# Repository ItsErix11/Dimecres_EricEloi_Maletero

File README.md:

View this project on [CADLAB.io](https://cadlab.io/project/29036). 

# Proyecto Maletero

## Autores
- Eric Trejo Sanchez (@ItsErix11)
- Eloi Ortega Ortiz (@EloiOrtega)

## Versió - v1.0 ## Curs - Assignatura de Disseny de PCBs amb KiCad - [Curs 2024-2025]

## Objetivo 
Nuestro objetivo es crear un sistema controlador del maletero de un coche que pueda cumplir las funciones de abrir y cerrar el maletero con un motor, desempañar el cristal de este y que se pueda abrir con un sensor con el pie en el caso de tener las manos ocupadas

## Requisitos i especificaciones
- Control del motor de apertura/cierre del maletero
- Sistema de calefacción para desempañar el cristal
- Sensor de movimiento para apertura sin contacto
- Interfaz CAN para comunicación con otros sistemas del coche
- Protección contra sobrecorriente en el control del motor

## Diagrama de bloques 

## Tabla de componentes
| Descripció | Manufacturer Number | Package | Datasheet | Proveïdor | Unitats |
|------------|--------------------|---------|----------|----------|---------|
| LDO Voltage Regulators 5A L Drop Pos Fixed Regs | LT1084CT-5 | TO-220 | https://eu.mouser.com/datasheet/2/609/1083ffe-3123432.pdf | DigiKey | 1 |
| MCU 32 KB FL 1536 RAM 25 I/O | PIC18F2580T-I/SO | SOIC-28 | https://eu.mouser.com/datasheet/2/268/39637d-3443674.pdf | DigiKey | 1 |
| Impulsor de motor Unipolar NMOS PWM 8-SO-PowerPad | DRV8870DDA | HTSSOP-8 | https://www.ti.com/lit/ds/symlink/drv8870.pdf?HQS=dis-dk-null-digikeymode-dsf-pf-null-wwe&ts=1745209885777 | DigiKey | 1 |
| CAN Interface IC Hi Spd CAN Transceiv | MCP2551-I/SN | SOIC-8 | https://eu.mouser.com/datasheet/2/268/20001667G-3441642.pdf | DigiKey | 1 |
| Operational Amplifiers - Op Amps LOW PWR SGL OP AMP A 926-LM321MF/NOPB | LM321MFX/NOPB | SOT-23-5 | https://www.ti.com/lit/ds/symlink/lm321.pdf?ts=1742974140204&ref_url=https%253A%252F%252Fwww.ti.com%252Fproduct%252FLM321%253FkeyMatch%253DLM321%2526tisearch%253Duniversal_search%2526usecase%253DGPN-ALT | DigiKey | 1 |

## Funcionalidades
1. **Control del maletero**:
   - Apertura y cierre mediante motor controlado por el MCU
   - Protección antipinch mediante detección de corriente
   
2. **Sistema de desempañado**:
   - Calefacción controlada por botones para regulación de temperatura
   
3. **Apertura sin contacto**:
   - Sensor de movimiento para detección del pie

4. **Interfaz de comunicación**:
   - Protocolo CAN para integración con otros sistemas del coche
   - Posibilidad de control remoto desde la llave o panel central

## Historial de cambios 
| Data | Autor | Branch | Descripció |
|------|------|--------|------------|
| 2025-04-24 | Eric | `main` | Orden final, final del readme |
| 2025-04-24 | Eloi | `main` | Ultima revisión |
| 2025-04-23 | Eric | `main` | Version final final |
| 2025-04-23 | Eric | `main` | Todos los arreglos del placement |
| 2025-04-22 | Eric | `main` | Textos de fabrica y reglas de diseño solucionado |
| 2025-04-22 | Eric | `main` | Orden de carpetas y referencia a autores (nosotros) |
| 2025-04-21 | Eric | `main` | Inicio presupuesto y continuación del readme |
| 2025-04-18 | Eloi | `main` | Actualización del layout |
| 2025-04-17 | Eloi | `main` | Actualización del layout y netclases |
| 2025-04-12 | Eric | `main` | Orden carpetas |
| 2025-04-12 | Eric | `main` | Diagrama completo |
| 2025-04-09 | Eric | `main` | Esquematico final y pasado al layout |
| 2025-04-09 | Eric | `main` | Orden del esquematico |
| 2025-04-09 | Eric | `main` | Esquematico compactado |
| 2025-04-09 | Eloi | `main` | Corrección de errores de clase |
| 2025-04-09 | Eric | `main` | DRC errores 0, warnings 25 |
| 2025-04-09 | Eloi | `main` | Ultimos ajustes de islas del GND |
| 2025-04-08 | Eloi | `main` | Actualización de huella |
| 2025-04-08 | Eric | `main` | Reglas de diseño, 0 errores y separación de componentes |
| 2025-04-08 | Eric | `main` | Par diferencial CAN |
| 2025-04-08 | Eloi | `main` | Corrección de reglas de diseño del layout | 
| 2025-04-04 | Eloi | `main` | Layout v1.2 acabado |
| 2025-04-02 | Eloi | `main` | Corrección de errores del layout |
| 2025-04-02 | Eric | `main` | Esquematico y diagrama acabados |
| 2025-04-01 | Eloi | `main` | Layout final v.1, routing terminado |
| 2025-04-01 | Eric | `main` | Arreglos del GNDPWR y GND |
| 2025-04-01 | Eloi | `main` | Actualización del layout, capas top suprimidas |
| 2025-04-01 | Eric | `main` | Capas de cobre del layout y DE-9 |
| 2025-04-01 | Eloi | `main` | Actualización del layout |
| 2025-04-01 | Eloi | `main` | Layout placement |
| 2025-04-01 | Eloi | `main` | Creación del layout |
| 2025-04-01 | Eric | `main` | Arreglos esquemático |
| 2025-04-01 | Eloi | `main` | Huellas añadidas al esquematico |
| 2025-04-01 | Eloi | `main` | Cambio de sensor en el esquemático |
| 2025-03-31 | Eric | `main` | Adición del DE-9 y regulador del sensor del esquemático|
| 2025-03-30 | Eloi | `main` | Corrección de errores del esquemático |
| 2025-03-30 | Eric | `main` | Esquemático ordenado |
| 2025-03-29 | Eloi | `main` | Corrección del switch y net lists del esquemático |
| 2025-03-29 | Eric | `main` | Mas correcciones del esquemático |
| 2025-03-27 | Eric | `main` | Correcciones de orden y conectores del esquemático|
| 2025-03-26 | Eloi | `main` | Adición de Net lists, corrección de errores y regulador de tensión del esquematico |
| 2025-03-25 | Eric | `main` | Conector del Program |
| 2025-03-25 | Eric | `main` | Diagrama de bloques añadido |
| 2025-03-25 | Eric | `main` | Rth mas disperso |
| 2025-03-25 | Eric | `main` | Corrección del CAN y separación |
| 2025-03-25 | Eric | `main` | Adición de condensadores de desacoplo |
| 2025-03-25 | Eloi | `main` | Versión casi final |
| 2025-03-25 | Eric | `main` | Transcriver CAN, casi todo el MCU completado |
| 2025-03-24 | Eloi | `main` | Corrección de errores |
| 2025-03-24 | Eloi | `main` | Resistencia termica añadida |
| 2025-03-24 | Eric | `main` | Pruebas del proyecto |
| 2025-03-24 | Eric | `main` | Cristal añadido |
| 2025-03-24 | Eric | `main` | Reorganización y corrección de errores |
| 2025-03-24 | Eloi | `main` | Etapa de regulación (LT1117) |
| 2025-03-24 | Eric | `main` | Adición de conectores |
| 2025-03-24 | Eric | `main` | Creación del proyecto |

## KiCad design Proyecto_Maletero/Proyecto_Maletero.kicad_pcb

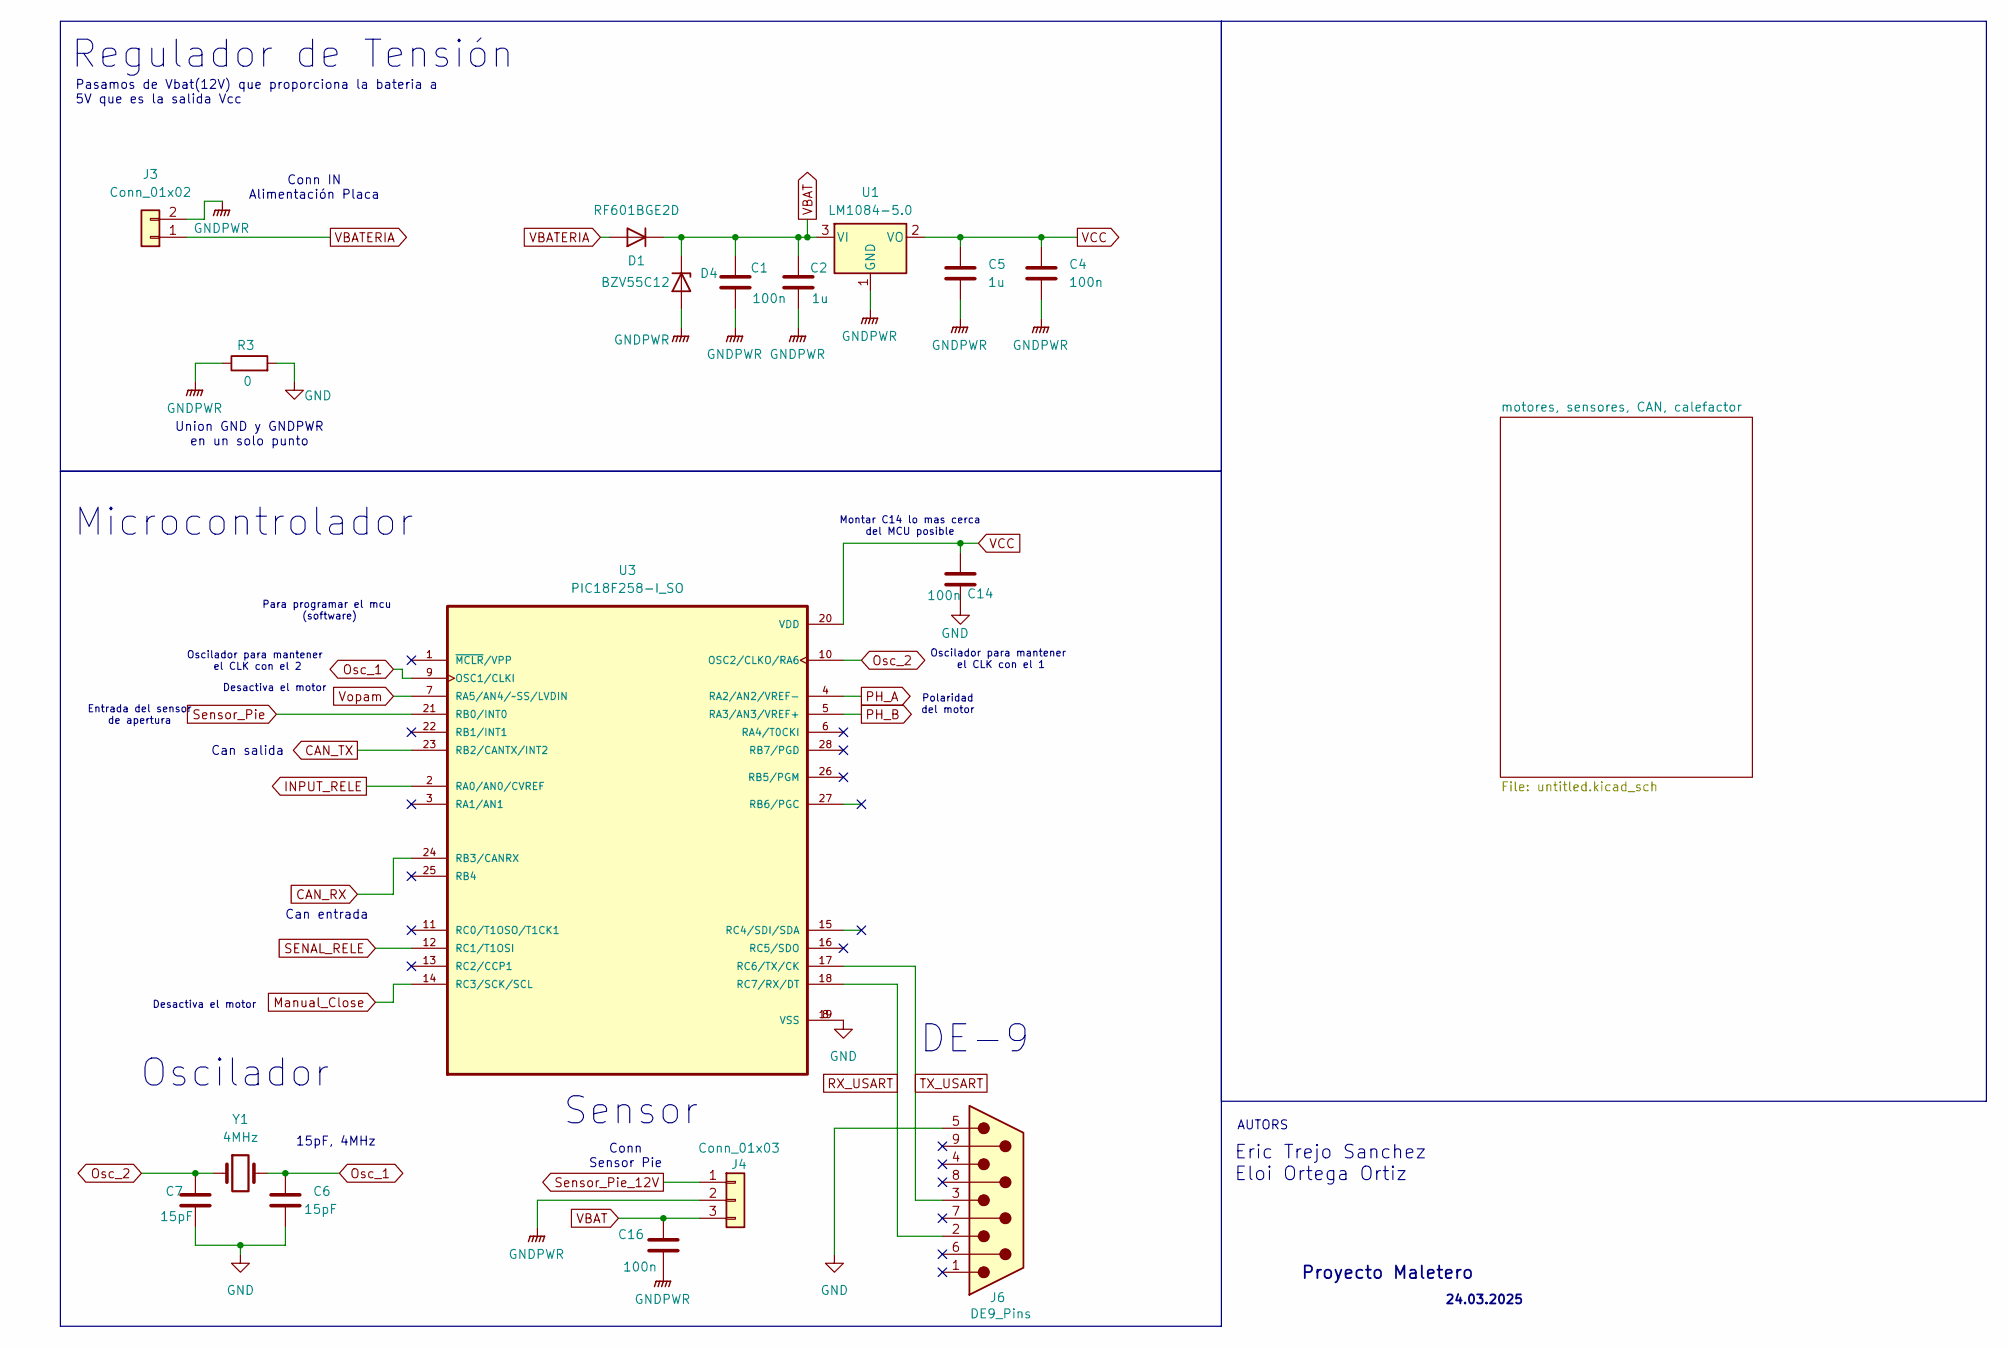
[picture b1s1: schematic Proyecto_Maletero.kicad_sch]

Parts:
C1, C4, C14, C16: 100n; C_0805_2012Metric
C2, C5: 1u; C_0805_2012Metric
C6, C7: 15pF; C_0805_2012Metric
D1: RF601BGE2D; D_0805_2012Metric
D4: BZV55C12; D_MiniMELF
J3: Conn_01x02; TerminalBlock_Phoenix_MKDS-1,5-2-5.08_1x02_P5.08mm_Horizont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
J4: Conn_01x03; TerminalBlock_Phoenix_MKDS-1,5-3_1x03_P5.00mm_Horizontal
J6: DE9_Pins; DSUB-9_Pins_Horizontal_P2.77x2.54mm_EdgePinOffset9.40mm
R3: 0
U1: LM1084-5.0; LT1117
U3: PIC18F258-I_SO; SOIC127P1030X265-28N
Y1: 4MHz; Crystal_SMD_HC49-SD

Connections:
CAN_RX: U3.24 (RB3/CANRX); also elsewhere on the board
CAN_TX: U3.23 (RB2/CANTX/INT2); also elsewhere on the board
GND: C6.2, C7.2, C14.1, J6.5, R3.2, U3.8 (VSS), U3.19 (VSS); also elsewhere on the board
GNDPWR: C1.2, C2.2, C4.2, C5.2, C16.1, D4.2 (A), J3.2, J4.2, R3.1, U1.1 (GND); also elsewhere on the board
INPUT_RELE: U3.2 (RA0/AN0/CVREF); also elsewhere on the board
Manual_Close: U3.14 (RC3/SCK/SCL); also elsewhere on the board
Osc_1: C6.1, U3.9 (OSC1/CLKI), Y1.2
Osc_2: C7.1, U3.10 (OSC2/CLKO/RA6), Y1.1
PH_A: U3.4 (RA2/AN2/VREF-); also elsewhere on the board
PH_B: U3.5 (RA3/AN3/VREF+); also elsewhere on the board
RX_USART: J6.2, U3.18 (RC7/RX/DT)
SENAL_RELE: U3.12 (RC1/T1OSI); also elsewhere on the board
Sensor_Pie: U3.21 (RB0/INT0); also elsewhere on the board
Sensor_Pie_12V: J4.1; also elsewhere on the board
TX_USART: J6.3, U3.17 (RC6/TX/CK)
VBAT: C1.1, C2.1, C16.2, D1.1 (K), D4.1 (K), J4.3, U1.3 (VI); also elsewhere on the board
VBATERIA: D1.2 (A), J3.1
VCC: C4.1, C5.1, C14.2, U1.2 (VO), U3.20 (VDD); also elsewhere on the board
Vopam: U3.7 (RA5/AN4/~SS/LVDIN); also elsewhere on the board

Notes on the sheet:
Desactiva el motor
Para programar el mcu (software)
Polaridad del motor
Eric Trejo Sanchez Eloi Ortega Ortiz
DE-9
Regulador de Tensión
Pasamos de Vbat(12V) que proporciona la bateria a 5V que es la salida Vcc
Microcontrolador
Sensor
Union GND y GNDPWR en un solo punto
15pF, 4MHz
Oscilador para mantener el CLK con el 1
Entrada del sensor de apertura
Can salida
Oscilador
Proyecto Maletero
Montar C14 lo mas cerca del MCU posible
Can entrada
AUTORS
24.03.2025
Oscilador para mantener el CLK con el 2
Conn IN Alimentación Placa
Conn Sensor Pie

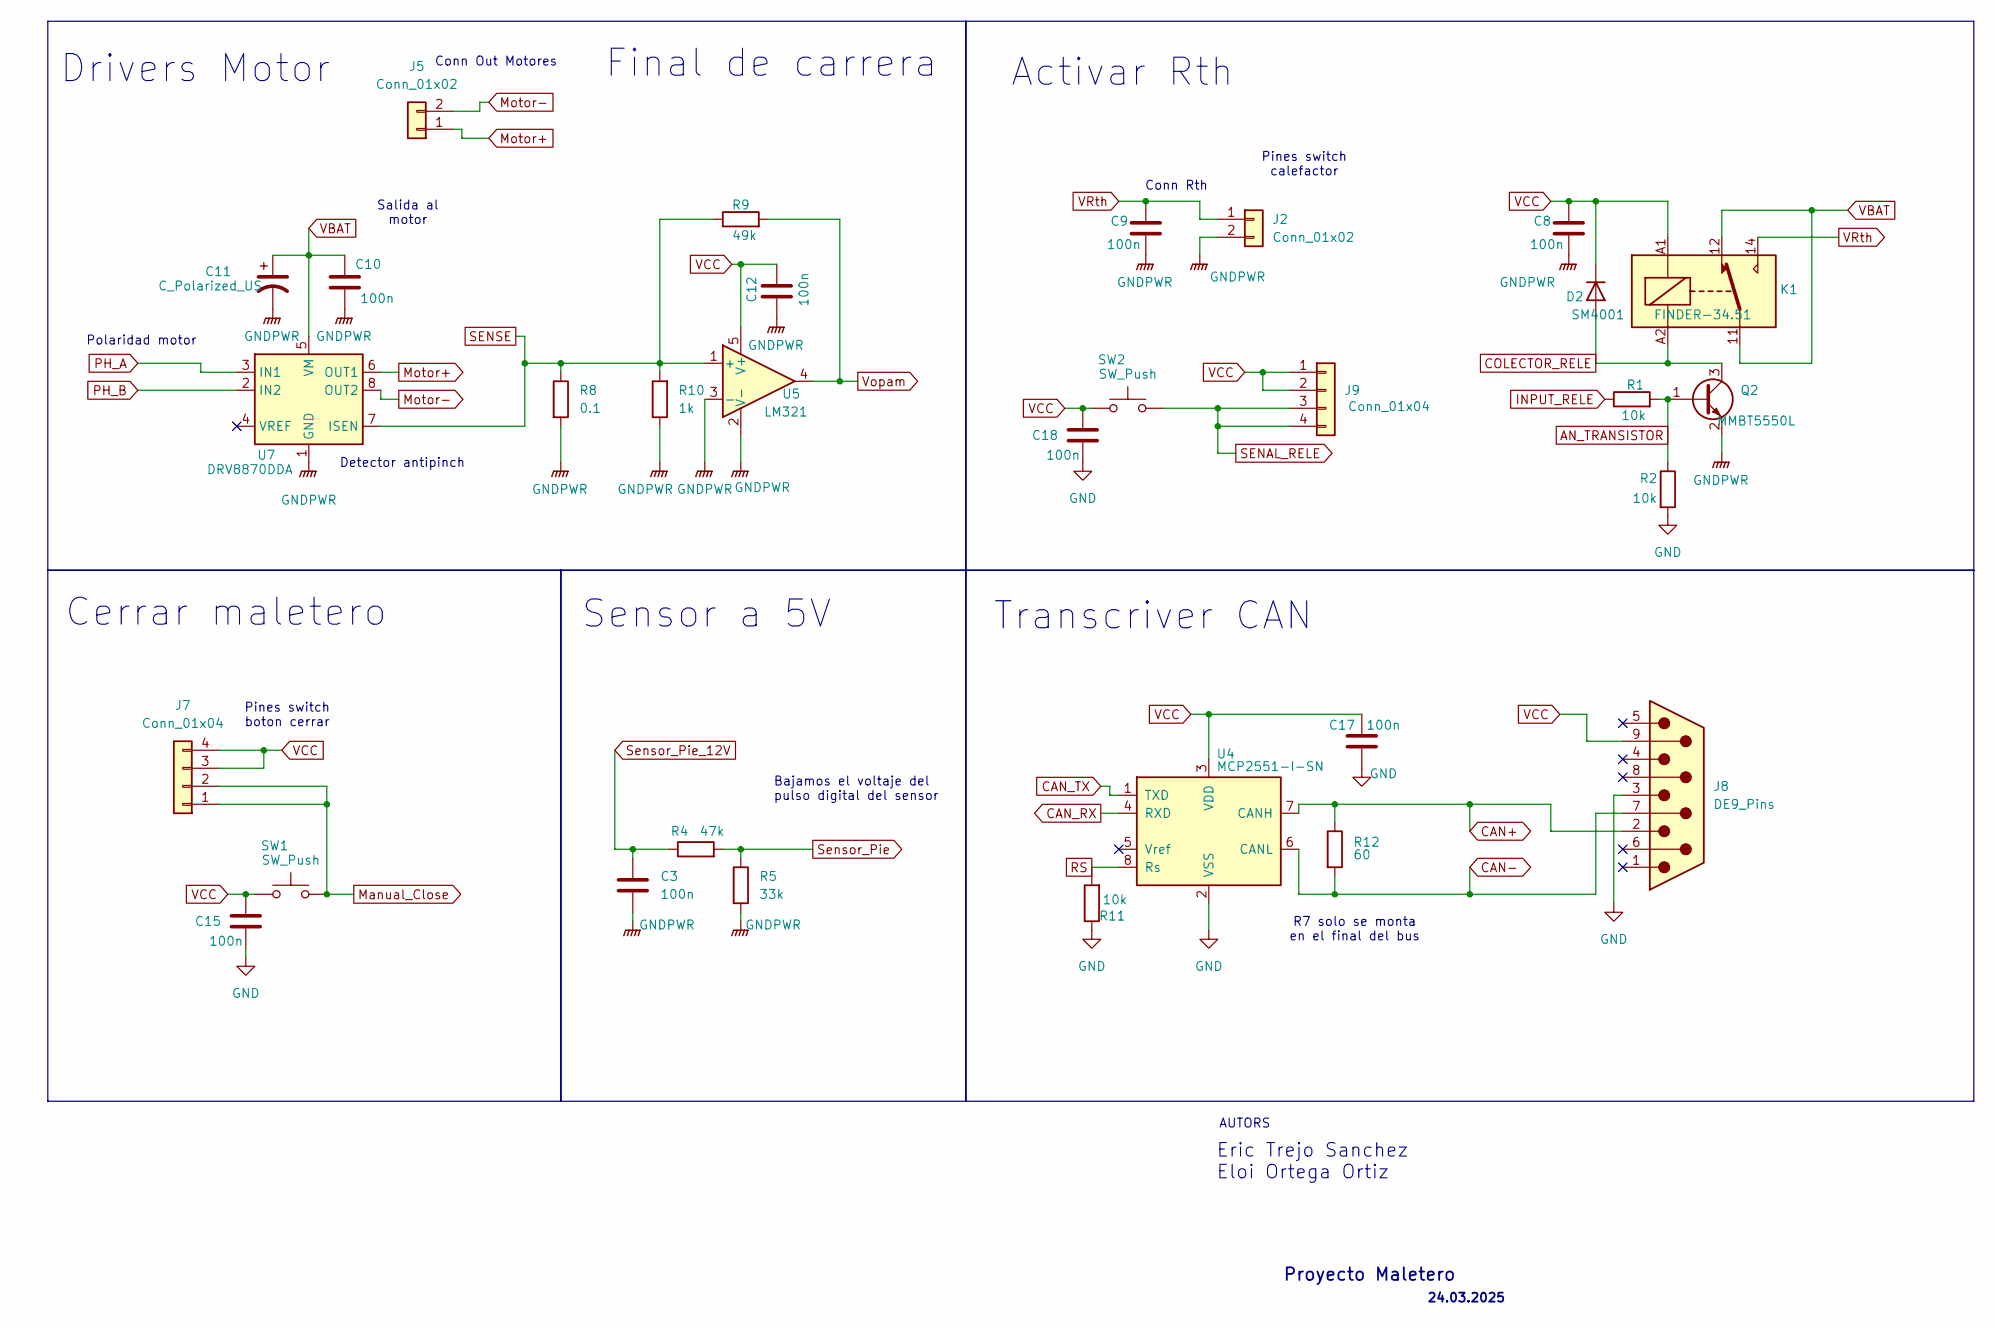
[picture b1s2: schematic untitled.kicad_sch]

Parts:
C3, C8, C9, C10, C12, C15, C17, C18: 100n; C_0805_2012Metric
C11: C_Polarized_US; CP_Elec_3x5.3
D2: SM4001; D_MELF
J2, J5: Conn_01x02; TerminalBlock_Phoenix_MKDS-1,5-2-5.08_1x02_P5.08mm_Horizont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
J7, J9: Conn_01x04; PinHeader_1x04_P2.54mm_Vertical
J8: DE9_Pins; DSUB-9_Pins_Horizontal_P2.77x2.54mm_EdgePinOffset9.40mm
K1: FINDER-34.51; Relay_SPDT_Finder_34.51_Vertical
Q2: MMBT5550L; SOT-23
R1, R2, R11: 10k; R_0805_2012Metric
R4: 47k; R_0805_2012Metric
R5: 33k; R_0805_2012Metric
R8: 0.1; R_0805_2012Metric
R9: 49k; R_0805_2012Metric
R10: 1k; R_0805_2012Metric
R12: 60; R_0805_2012Metric
SW1, SW2: SW_Push
U4: MCP2551-I-SN; SOIC-8_3.9x4.9mm_P1.27mm
U5: LM321; SOT-23-5
U7: DRV8870DDA; Texas_HTSOP-8-1EP_3.9x4.9mm_P1.27mm_EP2.95x4.9mm_Mask2.4x3.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

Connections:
AN_TRANSISTOR: Q2.1 (B), R1.2, R2.1
CAN+: J8.2, R12.1, U4.7 (CANH)
CAN-: J8.7, R12.2, U4.6 (CANL)
CAN_RX: U4.4 (RXD); also elsewhere on the board
CAN_TX: U4.1 (TXD); also elsewhere on the board
COLECTOR_RELE: D2.2 (A), K1.A2, Q2.3 (C)
GND: C15.1, C17.1, C18.1, J8.3, R2.2, R11.1, U4.2 (VSS); also elsewhere on the board
GNDPWR: C3.2, C8.2, C9.2, C10.1, C11.2, C12.2, J2.2, Q2.2 (E), R5.2, R8.2, R10.1, U5.2 (V-), U5.3 (-), U7.1 (GND), U7.9 (GND); also elsewhere on the board
INPUT_RELE: R1.1; also elsewhere on the board
Manual_Close: J7.1, J7.2, SW1.2; also elsewhere on the board
Motor+: J5.1, U7.6 (OUT1)
Motor-: J5.2, U7.8 (OUT2)
PH_A: U7.3 (IN1); also elsewhere on the board
PH_B: U7.2 (IN2); also elsewhere on the board
RS: R11.2, U4.8 (Rs)
SENAL_RELE: J9.3, J9.4, SW2.2; also elsewhere on the board
SENSE: R8.1, R9.1, R10.2, U5.1 (+), U7.7 (ISEN)
Sensor_Pie: R4.2, R5.1; also elsewhere on the board
Sensor_Pie_12V: C3.1, R4.1; also elsewhere on the board
VBAT: C10.2, C11.1, K1.11, K1.12, U7.5 (VM); also elsewhere on the board
VCC: C8.1, C12.1, C15.2, C17.2, C18.2, D2.1 (K), J7.3, J7.4, J8.9, J9.1, J9.2, K1.A1, SW1.1, SW2.1, U4.3 (VDD), U5.5 (V+); also elsewhere on the board
VRth: C9.1, J2.1, K1.14
Vopam: R9.2, U5.4; also elsewhere on the board

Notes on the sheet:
Transcriver CAN
Pines switch boton cerrar
Polaridad motor
R7 solo se monta en el final del bus
Final de carrera
Salida al motor
Drivers Motor
Activar Rth
AUTORS
24.03.2025
Proyecto Maletero
Detector antipinch
Cerrar maletero
Pines switch calefactor
Conn Out Motores
Sensor a 5V
Conn Rth
Eric Trejo Sanchez Eloi Ortega Ortiz
Bajamos el voltaje del pulso digital del sensor

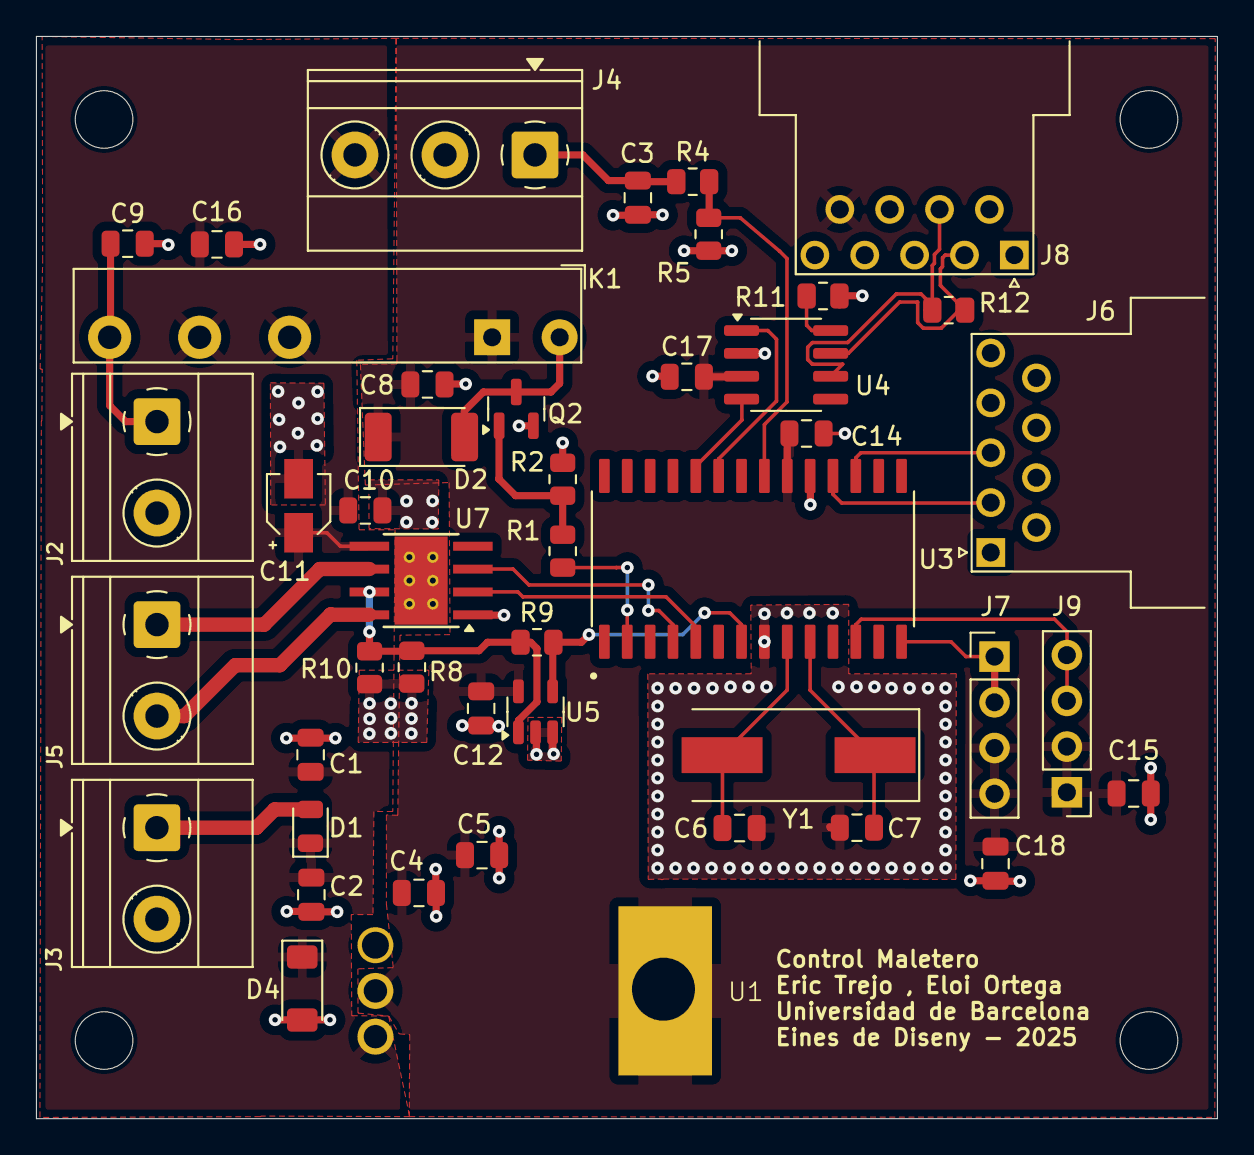
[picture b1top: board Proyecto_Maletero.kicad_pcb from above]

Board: 2 copper layers, 65.6 x 60.1 mm, 45 parts (0 on the bottom side), 28 nets.

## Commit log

2025-03-24 README
    He puesto nuestros nombres
2025-03-24 Creación proyecto
2025-03-24 Eliminación proyecto
2025-03-24 Adición conectores
2025-03-24 Etapa de regulacion (LT1117)
    Hemos añadido una etapa de regulación de VBAT.
2025-03-24 Compracion guardado
2025-03-24 Comprobación Guardado 2
2025-03-24 Reorganizacion y correccion de errores
2025-03-24 Actualizacion
2025-03-25 Cristal added
    Tengo que añadir las etiquetas del mcu
2025-03-25 Pines MCU y anotaciones
    Tengo que mirar la freq de funcionamiento para nuestro sistema y confirmar los pines que faltan
2025-03-25 Prueba
2025-03-25 Prueba 2
2025-03-25 Backlink to CADLAB.io has been added.
2025-03-25 Resistencia Termica
2025-03-25 Correccion de errores
2025-03-25 Etiquetas motor acabado
    Faltarian componentes pasivos
2025-03-25 Transcriver CAN, caso todo mcu
    Falta final de carrera
2025-03-25 Version casi final
    Anadiodo, final de carrera, seleccion de pines, y condensadores de desacoplamiento
2025-03-25 Correcciones Condensadores
2025-03-25 Corrección CAN y separación
    Hemos puesto una resistencia para los extremos del bus CAN. Tambien hemos separado los tags para que no se vea tan junto
2025-03-25 Rth menos enano
    Hemos expandido Rth
2025-03-26 Añadido diagrama de bloques
2025-03-26 Conector Program
2025-03-26 Añadir NET list,modificacion de erros,, y regulador
2025-03-27 Cambio de orden y posición de conn
    Tambien he añadido los DE-9, creo que el USART necesita un convertidor o algo asi, igual lo quitamos.
2025-03-29 Correcciones de la version anterior
    Falta cambiar los nets múltiples esos
2025-03-29 Mas correcciones
    Final de carrera, etc.
2025-03-29 Correccion switch y anadido las net list
    Hemos anadido un rele y un npn para controlar la Rth
2025-03-29 Orden
2025-03-30 Correccion errores
2025-03-31 DE-9 UART, regulador sensor, quitar program
    El program no se pone porque se programa a parte segun se dijo en clase
2025-03-31 Lo mismo pero guardando el proyecto
    Solo queda hacer la etapa de regulación del sensor y entramos al layout
2025-03-31 auctualizacion y cambio de sensor
2025-03-31 Añadido huellas
2025-03-31 Comiezo layaut
2025-03-31 Layout inicio
2025-04-01 Capas y DE-9
2025-04-01 Actulizacion layout
2025-04-01 GNDPWR
2025-04-01 Layout final v.1
2025-04-02 esquematico acabado y diagrama acabado
2025-04-02 Actualización README
2025-04-02 Actualizaciones y primeros pasos para correfir errores
2025-04-04 Layout v1.2 acabado
2025-04-04 Guardado
2025-04-08 Correcion de reglas de diseno
2025-04-08 Cerrar KICAD
2025-04-08 nets par diferencial
2025-04-08 saved
2025-04-08 Reglas de diseño, errores 0, separación del transcriver
    hay 108 warnings igualmente
2025-04-08 Algun cambio
2025-04-08 Actualizacion de huella y errores
2025-04-08 Ultimos ajustes de islas de gnd y huellas
2025-04-09 DRC errores 0 warnings 25
2025-04-09 actu
2025-04-09 Correccion de errores en clase
2025-04-09 Modificaciones de Clase
2025-04-09 Esquematico compactado
2025-04-09 Modificación del orden del esquematico
    puesto a punto
2025-04-09 Esquematico final y pasado al layout
2025-04-12 Diagrama completo
2025-04-12 Orden carpetas
2025-04-12 README actu
2025-04-17 Actualizacion layout
    Colocacion idonias de tornillos, simetrias y reduccion de avisos de 8 a 2
2025-04-17 NETCLASES
    Acabdo de modificar las net clases
2025-04-18 Actulizacion Placa
    Mover de9
2025-04-21 Inicio presupuesto y continuación readme
2025-04-22 Orden de carpetas, referencia a los autores layout (nosotros)
2025-04-22 Textos del fabricante y error de reglas de diseño solucionado
2025-04-23 Muchos arreglos de placement
2025-04-23 Version final final
2025-04-23 Ultimos cambios y revisiones
2025-04-24 Gebers
2025-04-24 Orden final, final readme
